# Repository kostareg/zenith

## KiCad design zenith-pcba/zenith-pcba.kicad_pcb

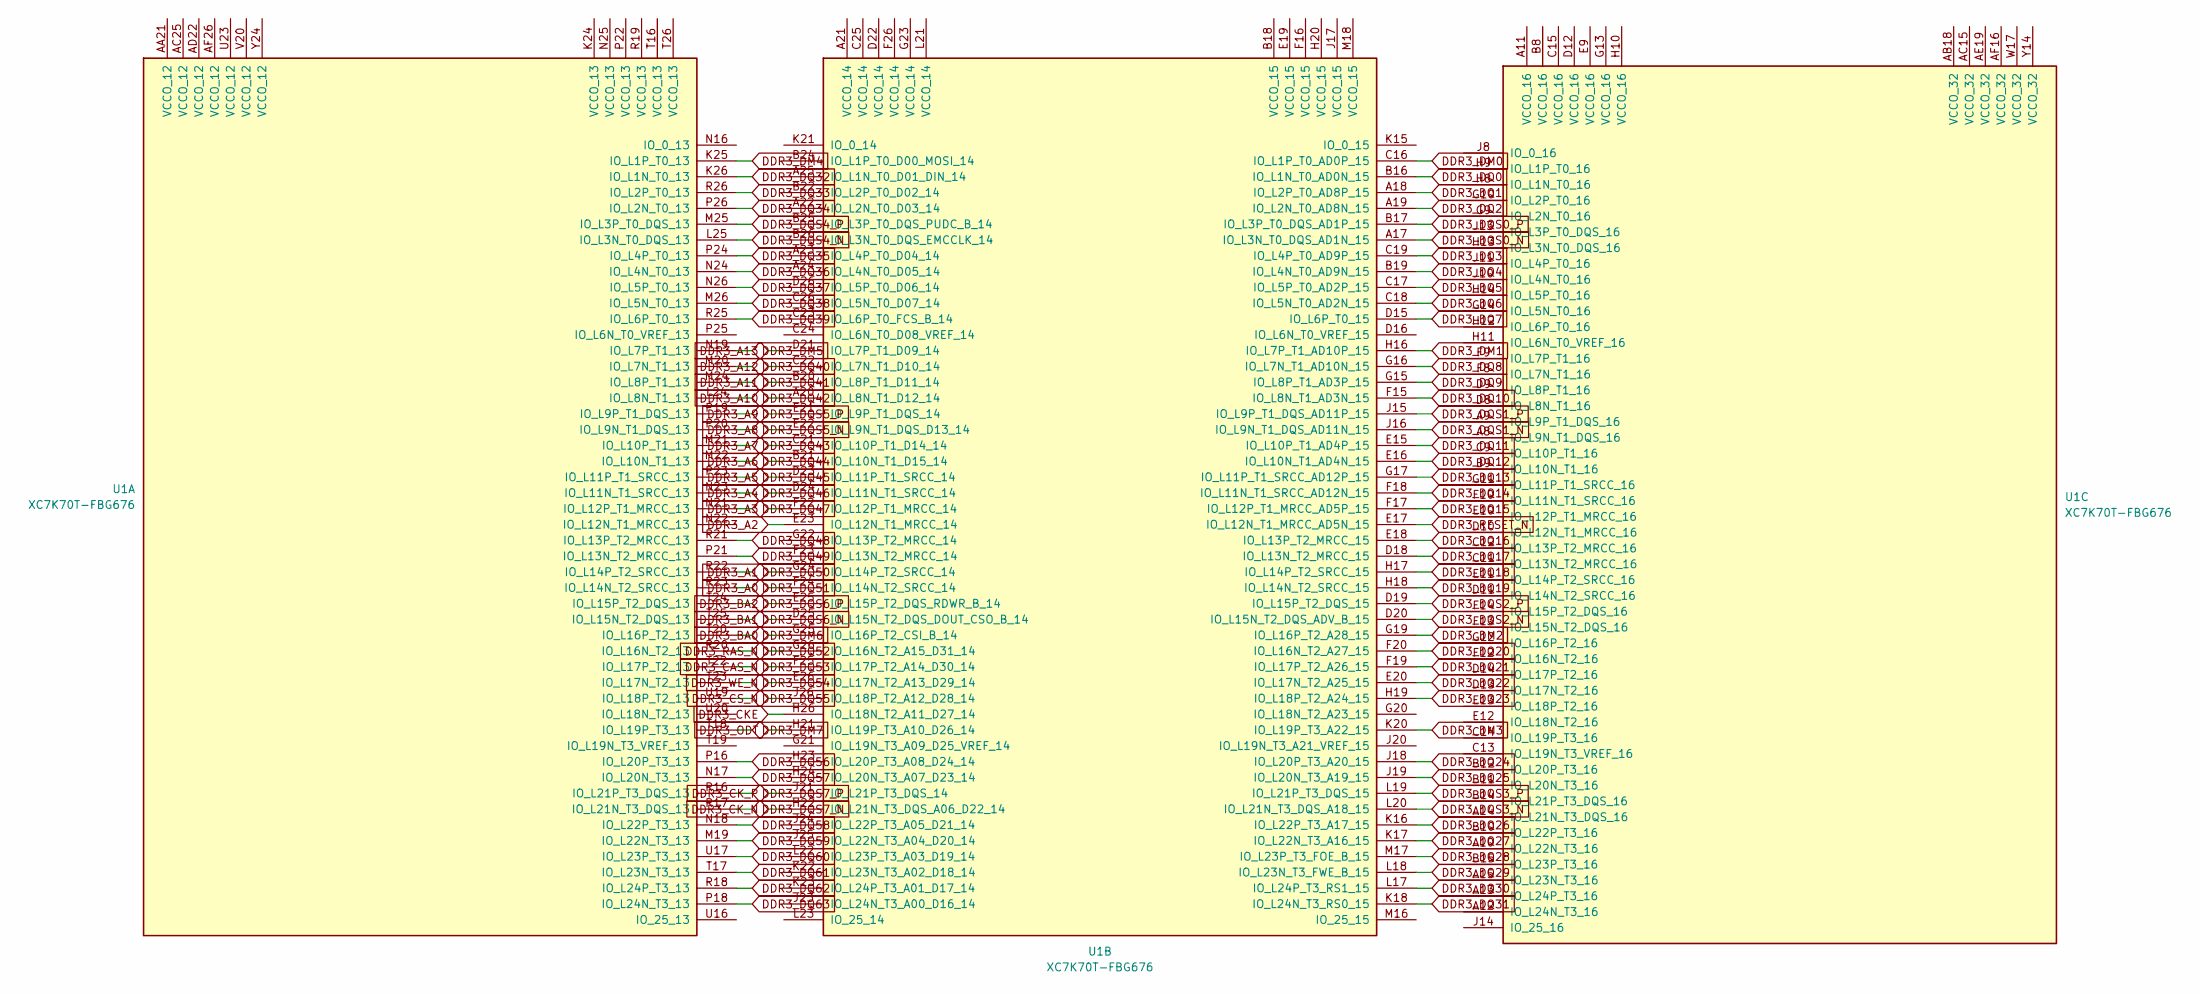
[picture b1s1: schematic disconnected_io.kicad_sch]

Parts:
U1: XC7K70T-FBG676; FBGA-676_L27.0-W27.0-R26-C26-P1.00-BL

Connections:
DDR3_A0: U1.F24 (IO_L14N_T2_SRCC_14); also elsewhere on the board
DDR3_A1: U1.G24 (IO_L14P_T2_SRCC_14); also elsewhere on the board
DDR3_A2: U1.E23 (IO_L12N_T1_MRCC_14); also elsewhere on the board
DDR3_A3: U1.F22 (IO_L12P_T1_MRCC_14); also elsewhere on the board
DDR3_A4: U1.D24 (IO_L11N_T1_SRCC_14); also elsewhere on the board
DDR3_A5: U1.D23 (IO_L11P_T1_SRCC_14); also elsewhere on the board
DDR3_A6: U1.B21 (IO_L10N_T1_D15_14); also elsewhere on the board
DDR3_A7: U1.C21 (IO_L10P_T1_D14_14); also elsewhere on the board
DDR3_A8: U1.E22 (IO_L9N_T1_DQS_D13_14); also elsewhere on the board
DDR3_A9: U1.E21 (IO_L9P_T1_DQS_14); also elsewhere on the board
DDR3_A10: U1.A20 (IO_L8N_T1_D12_14); also elsewhere on the board
DDR3_A11: U1.B20 (IO_L8P_T1_D11_14); also elsewhere on the board
DDR3_A12: U1.C22 (IO_L7N_T1_D10_14); also elsewhere on the board
DDR3_A13: U1.D21 (IO_L7P_T1_D09_14); also elsewhere on the board
DDR3_BA0: U1.G25 (IO_L16P_T2_CSI_B_14); also elsewhere on the board
DDR3_BA1: U1.D25 (IO_L15N_T2_DQS_DOUT_CSO_B_14); also elsewhere on the board
DDR3_BA2: U1.E25 (IO_L15P_T2_DQS_RDWR_B_14); also elsewhere on the board
DDR3_CAS_N: U1.F25 (IO_L17P_T2_A14_D30_14); also elsewhere on the board
DDR3_CKE: U1.H26 (IO_L18N_T2_A11_D27_14); also elsewhere on the board
DDR3_CK_N: U1.H22 (IO_L21N_T3_DQS_A06_D22_14); also elsewhere on the board
DDR3_CK_P: U1.J21 (IO_L21P_T3_DQS_14); also elsewhere on the board
DDR3_CS_N: U1.J26 (IO_L18P_T2_A12_D28_14); also elsewhere on the board
DDR3_DM0: U1.C16 (IO_L1P_T0_AD0P_15); also elsewhere on the board
DDR3_DM1: U1.H16 (IO_L7P_T1_AD10P_15); also elsewhere on the board
DDR3_DM2: U1.G19 (IO_L16P_T2_A28_15); also elsewhere on the board
DDR3_DM3: U1.K20 (IO_L19P_T3_A22_15); also elsewhere on the board
DDR3_DM4: U1.K25 (IO_L1P_T0_13); also elsewhere on the board
DDR3_DM5: U1.N19 (IO_L7P_T1_13); also elsewhere on the board
DDR3_DM6: U1.T20 (IO_L16P_T2_13); also elsewhere on the board
DDR3_DM7: U1.T18 (IO_L19P_T3_13); also elsewhere on the board
DDR3_DQ0: U1.B16 (IO_L1N_T0_AD0N_15); also elsewhere on the board
DDR3_DQ1: U1.A18 (IO_L2P_T0_AD8P_15); also elsewhere on the board
DDR3_DQ2: U1.A19 (IO_L2N_T0_AD8N_15); also elsewhere on the board
DDR3_DQ3: U1.C19 (IO_L4P_T0_AD9P_15); also elsewhere on the board
DDR3_DQ4: U1.B19 (IO_L4N_T0_AD9N_15); also elsewhere on the board
DDR3_DQ5: U1.C17 (IO_L5P_T0_AD2P_15); also elsewhere on the board
DDR3_DQ6: U1.C18 (IO_L5N_T0_AD2N_15); also elsewhere on the board
DDR3_DQ7: U1.D15 (IO_L6P_T0_15); also elsewhere on the board
DDR3_DQ8: U1.G16 (IO_L7N_T1_AD10N_15); also elsewhere on the board
DDR3_DQ9: U1.G15 (IO_L8P_T1_AD3P_15); also elsewhere on the board
DDR3_DQ10: U1.F15 (IO_L8N_T1_AD3N_15); also elsewhere on the board
DDR3_DQ11: U1.E15 (IO_L10P_T1_AD4P_15); also elsewhere on the board
DDR3_DQ12: U1.E16 (IO_L10N_T1_AD4N_15); also elsewhere on the board
DDR3_DQ13: U1.G17 (IO_L11P_T1_SRCC_AD12P_15); also elsewhere on the board
DDR3_DQ14: U1.F18 (IO_L11N_T1_SRCC_AD12N_15); also elsewhere on the board
DDR3_DQ15: U1.F17 (IO_L12P_T1_MRCC_AD5P_15); also elsewhere on the board
DDR3_DQ16: U1.E18 (IO_L13P_T2_MRCC_15); also elsewhere on the board
DDR3_DQ17: U1.D18 (IO_L13N_T2_MRCC_15); also elsewhere on the board
DDR3_DQ18: U1.H17 (IO_L14P_T2_SRCC_15); also elsewhere on the board
DDR3_DQ19: U1.H18 (IO_L14N_T2_SRCC_15); also elsewhere on the board
DDR3_DQ20: U1.F20 (IO_L16N_T2_A27_15); also elsewhere on the board
DDR3_DQ21: U1.F19 (IO_L17P_T2_A26_15); also elsewhere on the board
DDR3_DQ22: U1.E20 (IO_L17N_T2_A25_15); also elsewhere on the board
DDR3_DQ23: U1.H19 (IO_L18P_T2_A24_15); also elsewhere on the board
DDR3_DQ24: U1.J18 (IO_L20P_T3_A20_15); also elsewhere on the board
DDR3_DQ25: U1.J19 (IO_L20N_T3_A19_15); also elsewhere on the board
DDR3_DQ26: U1.K16 (IO_L22P_T3_A17_15); also elsewhere on the board
DDR3_DQ27: U1.K17 (IO_L22N_T3_A16_15); also elsewhere on the board
DDR3_DQ28: U1.M17 (IO_L23P_T3_FOE_B_15); also elsewhere on the board
DDR3_DQ29: U1.L18 (IO_L23N_T3_FWE_B_15); also elsewhere on the board
DDR3_DQ30: U1.L17 (IO_L24P_T3_RS1_15); also elsewhere on the board
DDR3_DQ31: U1.K18 (IO_L24N_T3_RS0_15); also elsewhere on the board
DDR3_DQ32: U1.K26 (IO_L1N_T0_13); also elsewhere on the board
DDR3_DQ33: U1.R26 (IO_L2P_T0_13); also elsewhere on the board
DDR3_DQ34: U1.P26 (IO_L2N_T0_13); also elsewhere on the board
DDR3_DQ35: U1.P24 (IO_L4P_T0_13); also elsewhere on the board
DDR3_DQ36: U1.N24 (IO_L4N_T0_13); also elsewhere on the board
DDR3_DQ37: U1.N26 (IO_L5P_T0_13); also elsewhere on the board
DDR3_DQ38: U1.M26 (IO_L5N_T0_13); also elsewhere on the board
DDR3_DQ39: U1.R25 (IO_L6P_T0_13); also elsewhere on the board
DDR3_DQ40: U1.M20 (IO_L7N_T1_13); also elsewhere on the board
DDR3_DQ41: U1.M24 (IO_L8P_T1_13); also elsewhere on the board
DDR3_DQ42: U1.L24 (IO_L8N_T1_13); also elsewhere on the board
DDR3_DQ43: U1.M21 (IO_L10P_T1_13); also elsewhere on the board
DDR3_DQ44: U1.M22 (IO_L10N_T1_13); also elsewhere on the board
DDR3_DQ45: U1.P23 (IO_L11P_T1_SRCC_13); also elsewhere on the board
DDR3_DQ46: U1.N23 (IO_L11N_T1_SRCC_13); also elsewhere on the board
DDR3_DQ47: U1.N21 (IO_L12P_T1_MRCC_13); also elsewhere on the board
DDR3_DQ48: U1.R21 (IO_L13P_T2_MRCC_13); also elsewhere on the board
DDR3_DQ49: U1.P21 (IO_L13N_T2_MRCC_13); also elsewhere on the board
DDR3_DQ50: U1.R22 (IO_L14P_T2_SRCC_13); also elsewhere on the board
DDR3_DQ51: U1.R23 (IO_L14N_T2_SRCC_13); also elsewhere on the board
DDR3_DQ52: U1.R20 (IO_L16N_T2_13); also elsewhere on the board
DDR3_DQ53: U1.T22 (IO_L17P_T2_13); also elsewhere on the board
DDR3_DQ54: U1.T23 (IO_L17N_T2_13); also elsewhere on the board
DDR3_DQ55: U1.U19 (IO_L18P_T2_13); also elsewhere on the board
DDR3_DQ56: U1.P16 (IO_L20P_T3_13); also elsewhere on the board
DDR3_DQ57: U1.N17 (IO_L20N_T3_13); also elsewhere on the board
DDR3_DQ58: U1.N18 (IO_L22P_T3_13); also elsewhere on the board
DDR3_DQ59: U1.M19 (IO_L22N_T3_13); also elsewhere on the board
DDR3_DQ60: U1.U17 (IO_L23P_T3_13); also elsewhere on the board
DDR3_DQ61: U1.T17 (IO_L23N_T3_13); also elsewhere on the board
DDR3_DQ62: U1.R18 (IO_L24P_T3_13); also elsewhere on the board
DDR3_DQ63: U1.P18 (IO_L24N_T3_13); also elsewhere on the board
DDR3_DQS0_N: U1.A17 (IO_L3N_T0_DQS_AD1N_15); also elsewhere on the board
DDR3_DQS0_P: U1.B17 (IO_L3P_T0_DQS_AD1P_15); also elsewhere on the board
DDR3_DQS1_N: U1.J16 (IO_L9N_T1_DQS_AD11N_15); also elsewhere on the board
DDR3_DQS1_P: U1.J15 (IO_L9P_T1_DQS_AD11P_15); also elsewhere on the board
DDR3_DQS2_N: U1.D20 (IO_L15N_T2_DQS_ADV_B_15); also elsewhere on the board
DDR3_DQS2_P: U1.D19 (IO_L15P_T2_DQS_15); also elsewhere on the board
DDR3_DQS3_N: U1.L20 (IO_L21N_T3_DQS_A18_15); also elsewhere on the board
DDR3_DQS3_P: U1.L19 (IO_L21P_T3_DQS_15); also elsewhere on the board
DDR3_DQS4_N: U1.L25 (IO_L3N_T0_DQS_13); also elsewhere on the board
DDR3_DQS4_P: U1.M25 (IO_L3P_T0_DQS_13); also elsewhere on the board
DDR3_DQS5_N: U1.P20 (IO_L9N_T1_DQS_13); also elsewhere on the board
DDR3_DQS5_P: U1.P19 (IO_L9P_T1_DQS_13); also elsewhere on the board
DDR3_DQS6_N: U1.T25 (IO_L15N_T2_DQS_13); also elsewhere on the board
DDR3_DQS6_P: U1.T24 (IO_L15P_T2_DQS_13); also elsewhere on the board
DDR3_DQS7_N: U1.R17 (IO_L21N_T3_DQS_13); also elsewhere on the board
DDR3_DQS7_P: U1.R16 (IO_L21P_T3_DQS_13); also elsewhere on the board
DDR3_ODT: U1.H21 (IO_L19P_T3_A10_D26_14); also elsewhere on the board
DDR3_RAS_N: U1.G26 (IO_L16N_T2_A15_D31_14); also elsewhere on the board
DDR3_RESET_N: U1.E17 (IO_L12N_T1_MRCC_AD5N_15); also elsewhere on the board
DDR3_WE_N: U1.E26 (IO_L17N_T2_A13_D29_14); also elsewhere on the board

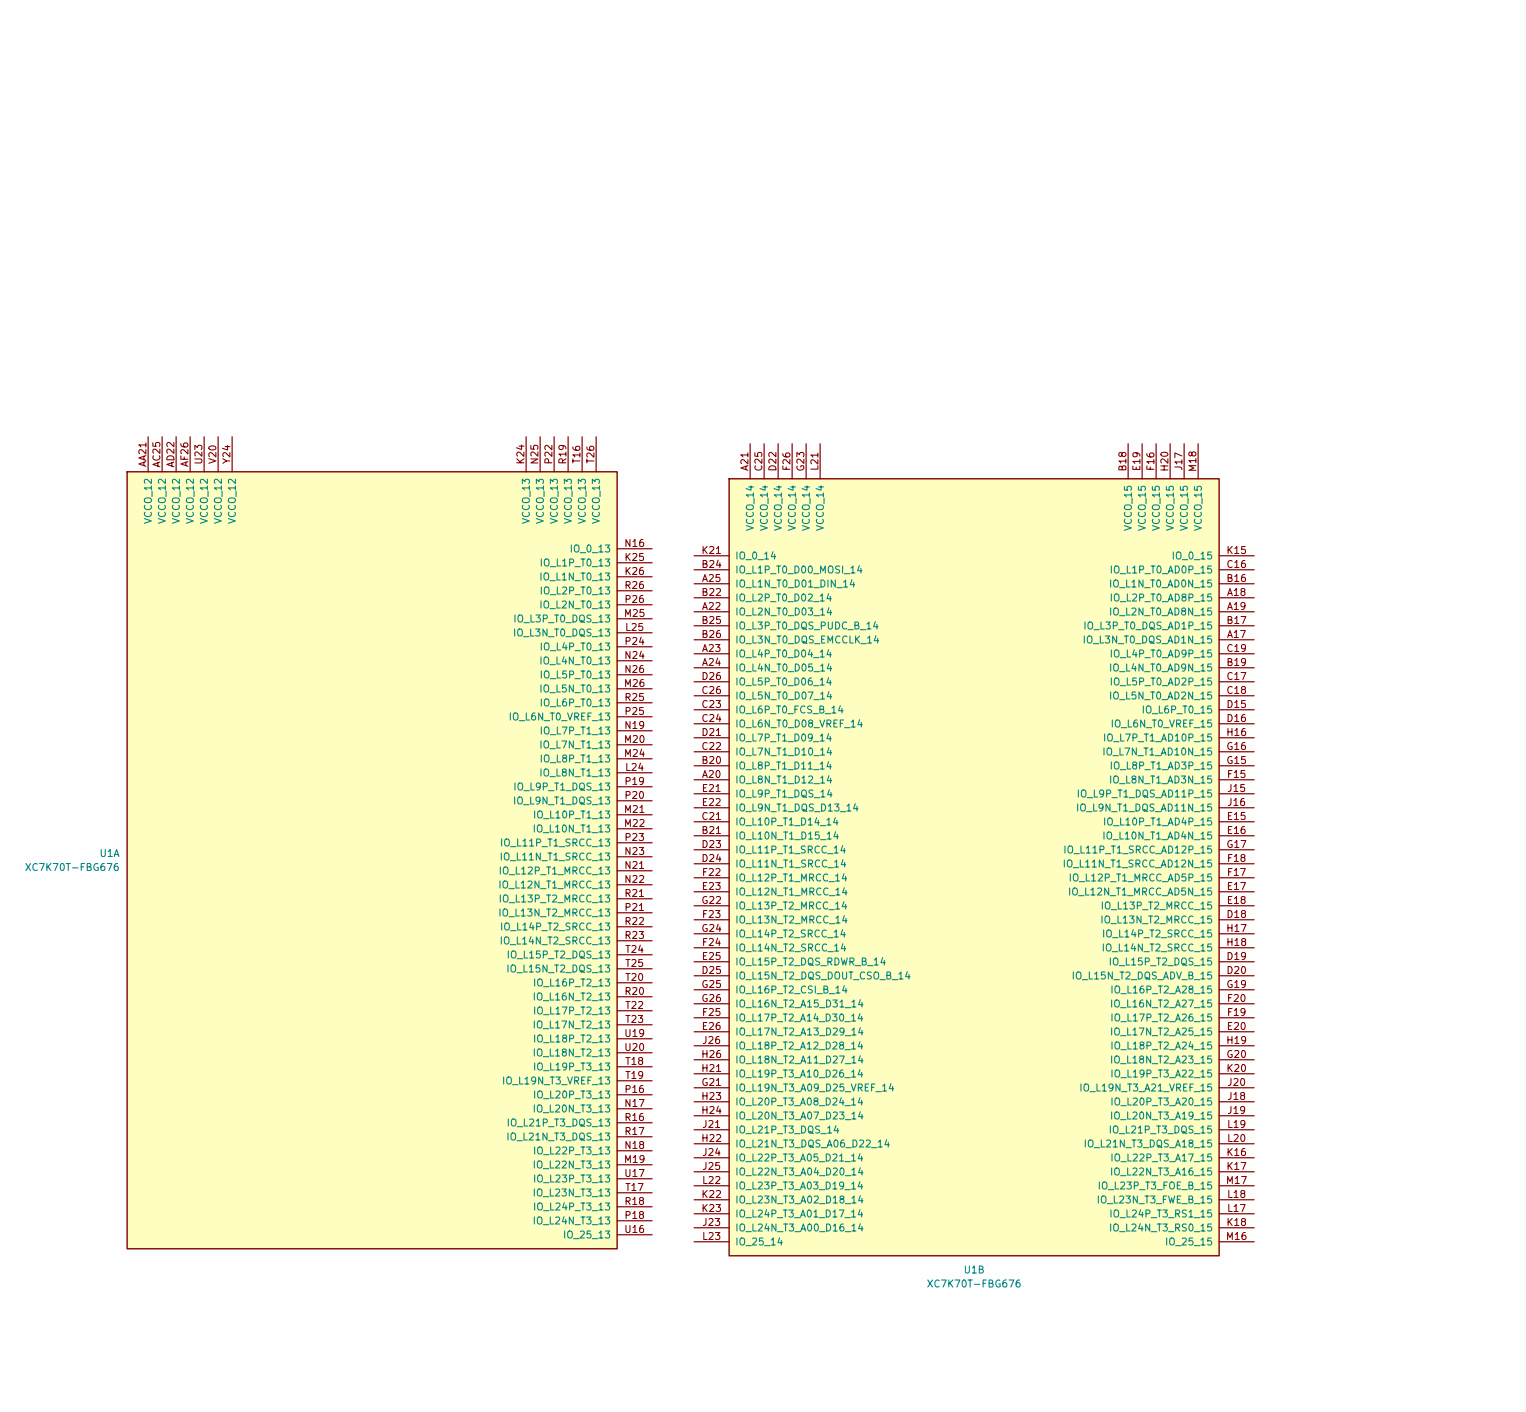
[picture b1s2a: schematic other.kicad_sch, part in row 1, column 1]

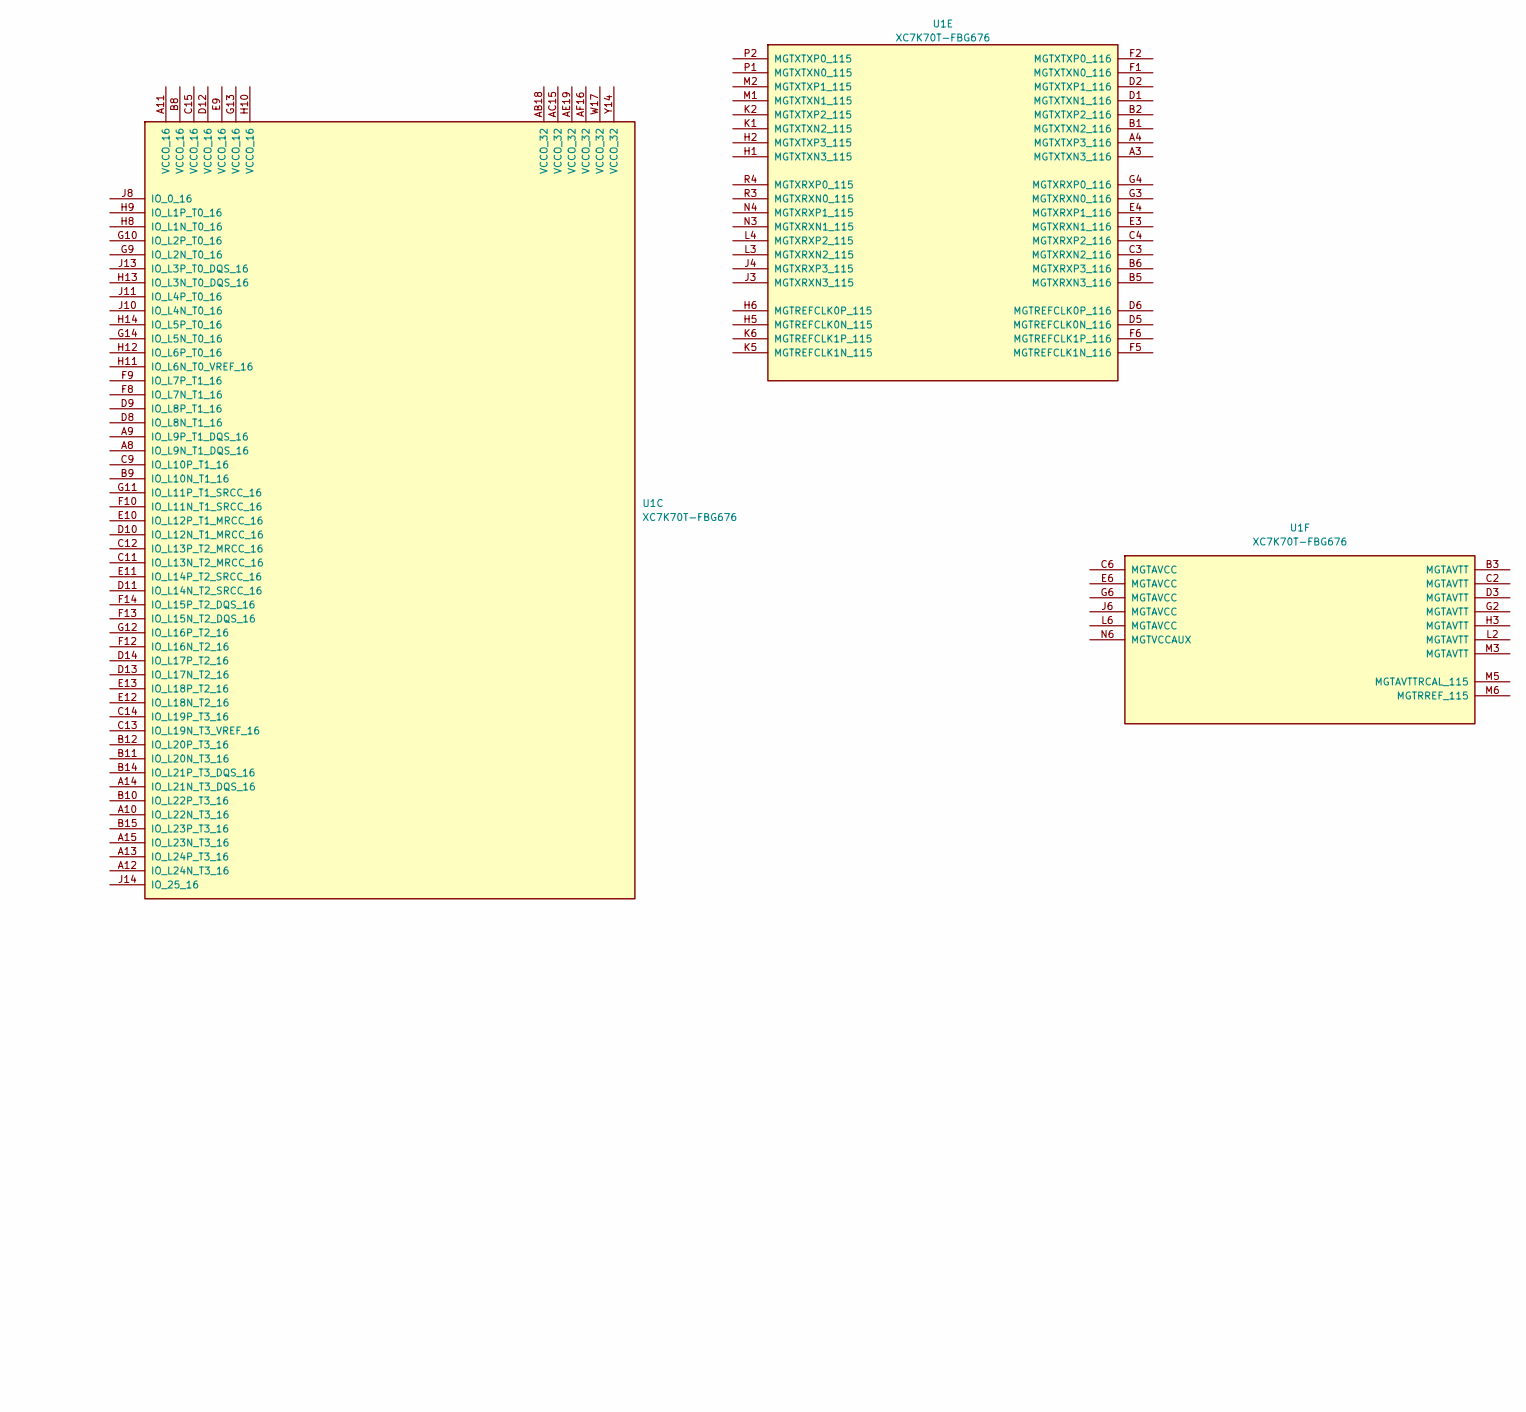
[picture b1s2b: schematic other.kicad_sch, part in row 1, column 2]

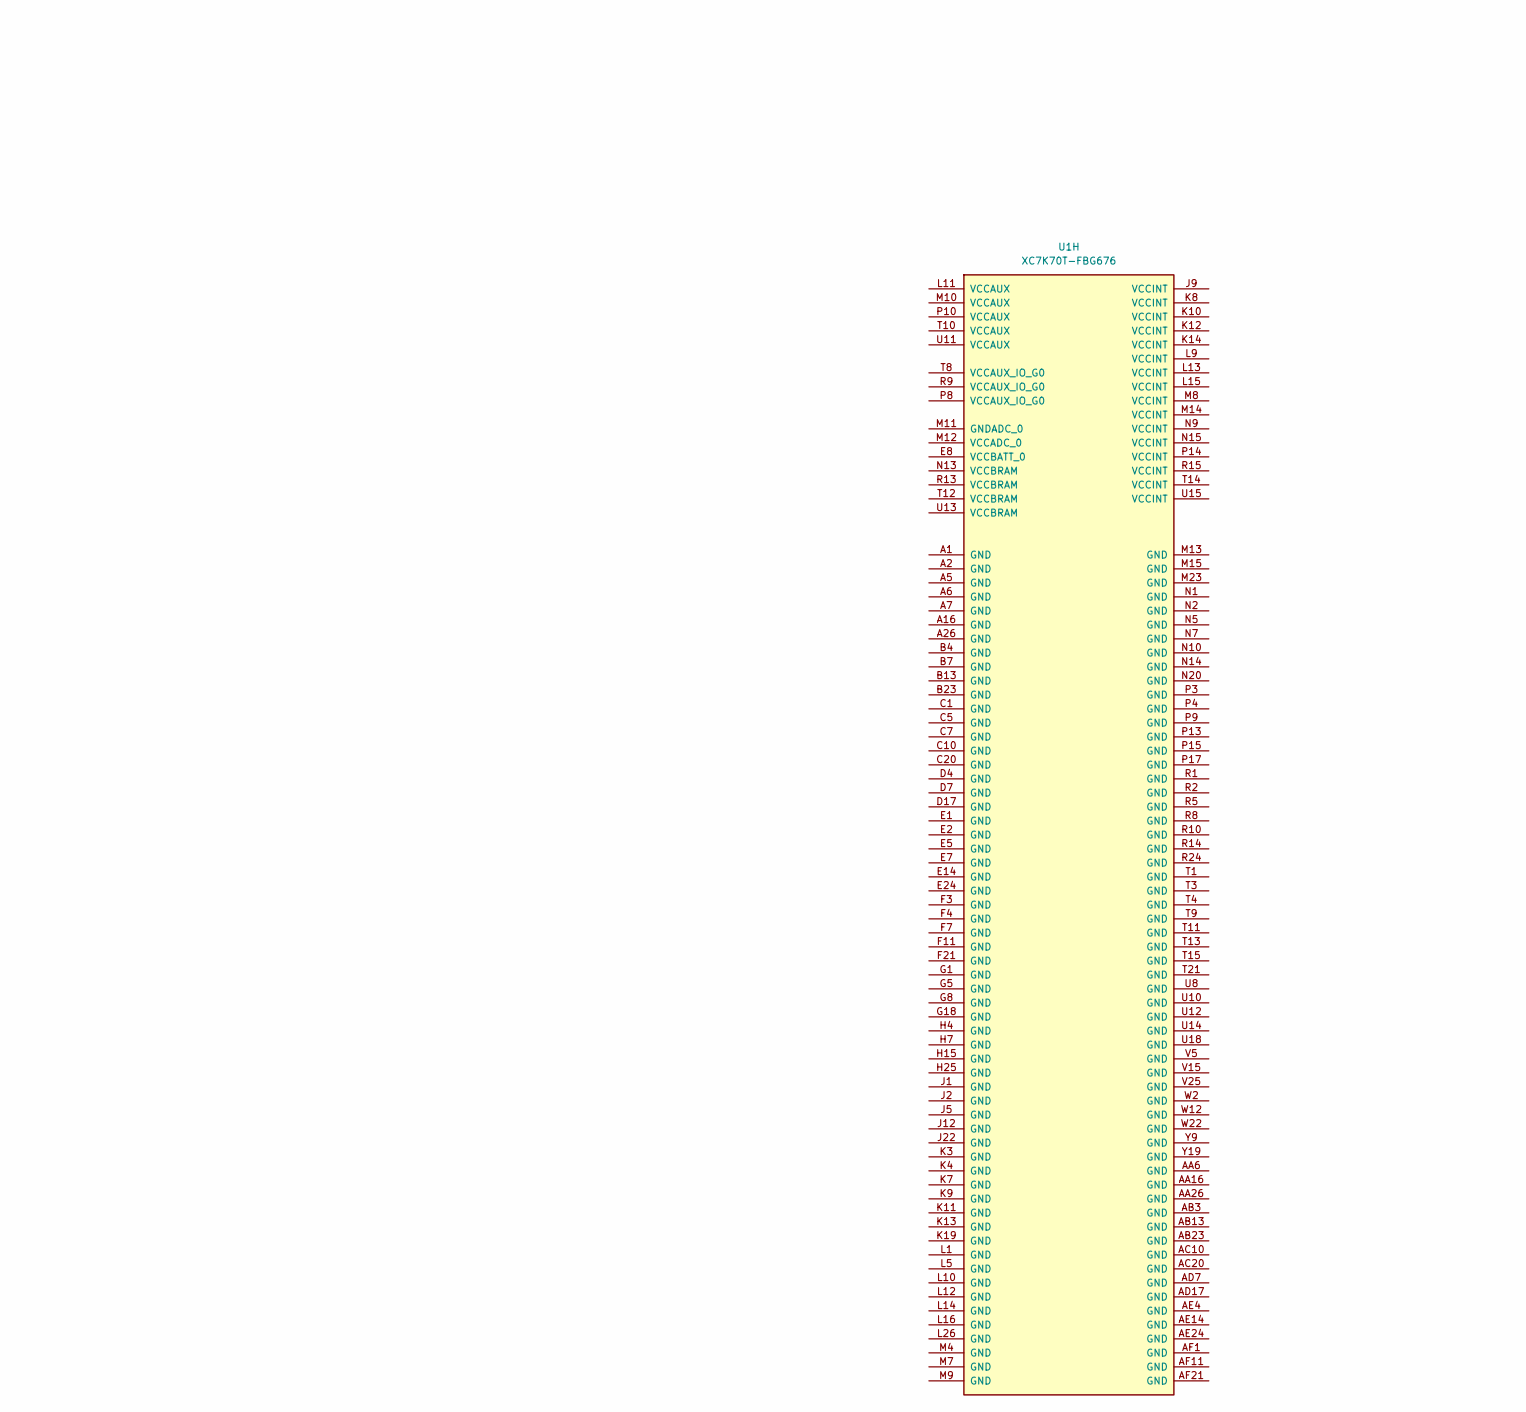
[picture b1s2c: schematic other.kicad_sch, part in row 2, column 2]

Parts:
U1: XC7K70T-FBG676; FBGA-676_L27.0-W27.0-R26-C26-P1.00-BL

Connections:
DDR3_A0: U1.F24 (IO_L14N_T2_SRCC_14); also elsewhere on the board
DDR3_A1: U1.G24 (IO_L14P_T2_SRCC_14); also elsewhere on the board
DDR3_A2: U1.E23 (IO_L12N_T1_MRCC_14); also elsewhere on the board
DDR3_A3: U1.F22 (IO_L12P_T1_MRCC_14); also elsewhere on the board
DDR3_A4: U1.D24 (IO_L11N_T1_SRCC_14); also elsewhere on the board
DDR3_A5: U1.D23 (IO_L11P_T1_SRCC_14); also elsewhere on the board
DDR3_A6: U1.B21 (IO_L10N_T1_D15_14); also elsewhere on the board
DDR3_A7: U1.C21 (IO_L10P_T1_D14_14); also elsewhere on the board
DDR3_A8: U1.E22 (IO_L9N_T1_DQS_D13_14); also elsewhere on the board
DDR3_A9: U1.E21 (IO_L9P_T1_DQS_14); also elsewhere on the board
DDR3_A10: U1.A20 (IO_L8N_T1_D12_14); also elsewhere on the board
DDR3_A11: U1.B20 (IO_L8P_T1_D11_14); also elsewhere on the board
DDR3_A12: U1.C22 (IO_L7N_T1_D10_14); also elsewhere on the board
DDR3_A13: U1.D21 (IO_L7P_T1_D09_14); also elsewhere on the board
DDR3_BA0: U1.G25 (IO_L16P_T2_CSI_B_14); also elsewhere on the board
DDR3_BA1: U1.D25 (IO_L15N_T2_DQS_DOUT_CSO_B_14); also elsewhere on the board
DDR3_BA2: U1.E25 (IO_L15P_T2_DQS_RDWR_B_14); also elsewhere on the board
DDR3_CAS_N: U1.F25 (IO_L17P_T2_A14_D30_14); also elsewhere on the board
DDR3_CKE: U1.H26 (IO_L18N_T2_A11_D27_14); also elsewhere on the board
DDR3_CK_N: U1.H22 (IO_L21N_T3_DQS_A06_D22_14); also elsewhere on the board
DDR3_CK_P: U1.J21 (IO_L21P_T3_DQS_14); also elsewhere on the board
DDR3_CS_N: U1.J26 (IO_L18P_T2_A12_D28_14); also elsewhere on the board
DDR3_DM0: U1.C16 (IO_L1P_T0_AD0P_15); also elsewhere on the board
DDR3_DM1: U1.H16 (IO_L7P_T1_AD10P_15); also elsewhere on the board
DDR3_DM2: U1.G19 (IO_L16P_T2_A28_15); also elsewhere on the board
DDR3_DM3: U1.K20 (IO_L19P_T3_A22_15); also elsewhere on the board
DDR3_DM4: U1.K25 (IO_L1P_T0_13); also elsewhere on the board
DDR3_DM5: U1.N19 (IO_L7P_T1_13); also elsewhere on the board
DDR3_DM6: U1.T20 (IO_L16P_T2_13); also elsewhere on the board
DDR3_DM7: U1.T18 (IO_L19P_T3_13); also elsewhere on the board
DDR3_DQ0: U1.B16 (IO_L1N_T0_AD0N_15); also elsewhere on the board
DDR3_DQ1: U1.A18 (IO_L2P_T0_AD8P_15); also elsewhere on the board
DDR3_DQ2: U1.A19 (IO_L2N_T0_AD8N_15); also elsewhere on the board
DDR3_DQ3: U1.C19 (IO_L4P_T0_AD9P_15); also elsewhere on the board
DDR3_DQ4: U1.B19 (IO_L4N_T0_AD9N_15); also elsewhere on the board
DDR3_DQ5: U1.C17 (IO_L5P_T0_AD2P_15); also elsewhere on the board
DDR3_DQ6: U1.C18 (IO_L5N_T0_AD2N_15); also elsewhere on the board
DDR3_DQ7: U1.D15 (IO_L6P_T0_15); also elsewhere on the board
DDR3_DQ8: U1.G16 (IO_L7N_T1_AD10N_15); also elsewhere on the board
DDR3_DQ9: U1.G15 (IO_L8P_T1_AD3P_15); also elsewhere on the board
DDR3_DQ10: U1.F15 (IO_L8N_T1_AD3N_15); also elsewhere on the board
DDR3_DQ11: U1.E15 (IO_L10P_T1_AD4P_15); also elsewhere on the board
DDR3_DQ12: U1.E16 (IO_L10N_T1_AD4N_15); also elsewhere on the board
DDR3_DQ13: U1.G17 (IO_L11P_T1_SRCC_AD12P_15); also elsewhere on the board
DDR3_DQ14: U1.F18 (IO_L11N_T1_SRCC_AD12N_15); also elsewhere on the board
DDR3_DQ15: U1.F17 (IO_L12P_T1_MRCC_AD5P_15); also elsewhere on the board
DDR3_DQ16: U1.E18 (IO_L13P_T2_MRCC_15); also elsewhere on the board
DDR3_DQ17: U1.D18 (IO_L13N_T2_MRCC_15); also elsewhere on the board
DDR3_DQ18: U1.H17 (IO_L14P_T2_SRCC_15); also elsewhere on the board
DDR3_DQ19: U1.H18 (IO_L14N_T2_SRCC_15); also elsewhere on the board
DDR3_DQ20: U1.F20 (IO_L16N_T2_A27_15); also elsewhere on the board
DDR3_DQ21: U1.F19 (IO_L17P_T2_A26_15); also elsewhere on the board
DDR3_DQ22: U1.E20 (IO_L17N_T2_A25_15); also elsewhere on the board
DDR3_DQ23: U1.H19 (IO_L18P_T2_A24_15); also elsewhere on the board
DDR3_DQ24: U1.J18 (IO_L20P_T3_A20_15); also elsewhere on the board
DDR3_DQ25: U1.J19 (IO_L20N_T3_A19_15); also elsewhere on the board
DDR3_DQ26: U1.K16 (IO_L22P_T3_A17_15); also elsewhere on the board
DDR3_DQ27: U1.K17 (IO_L22N_T3_A16_15); also elsewhere on the board
DDR3_DQ28: U1.M17 (IO_L23P_T3_FOE_B_15); also elsewhere on the board
DDR3_DQ29: U1.L18 (IO_L23N_T3_FWE_B_15); also elsewhere on the board
DDR3_DQ30: U1.L17 (IO_L24P_T3_RS1_15); also elsewhere on the board
DDR3_DQ31: U1.K18 (IO_L24N_T3_RS0_15); also elsewhere on the board
DDR3_DQ32: U1.K26 (IO_L1N_T0_13); also elsewhere on the board
DDR3_DQ33: U1.R26 (IO_L2P_T0_13); also elsewhere on the board
DDR3_DQ34: U1.P26 (IO_L2N_T0_13); also elsewhere on the board
DDR3_DQ35: U1.P24 (IO_L4P_T0_13); also elsewhere on the board
DDR3_DQ36: U1.N24 (IO_L4N_T0_13); also elsewhere on the board
DDR3_DQ37: U1.N26 (IO_L5P_T0_13); also elsewhere on the board
DDR3_DQ38: U1.M26 (IO_L5N_T0_13); also elsewhere on the board
DDR3_DQ39: U1.R25 (IO_L6P_T0_13); also elsewhere on the board
DDR3_DQ40: U1.M20 (IO_L7N_T1_13); also elsewhere on the board
DDR3_DQ41: U1.M24 (IO_L8P_T1_13); also elsewhere on the board
DDR3_DQ42: U1.L24 (IO_L8N_T1_13); also elsewhere on the board
DDR3_DQ43: U1.M21 (IO_L10P_T1_13); also elsewhere on the board
DDR3_DQ44: U1.M22 (IO_L10N_T1_13); also elsewhere on the board
DDR3_DQ45: U1.P23 (IO_L11P_T1_SRCC_13); also elsewhere on the board
DDR3_DQ46: U1.N23 (IO_L11N_T1_SRCC_13); also elsewhere on the board
DDR3_DQ47: U1.N21 (IO_L12P_T1_MRCC_13); also elsewhere on the board
DDR3_DQ48: U1.R21 (IO_L13P_T2_MRCC_13); also elsewhere on the board
DDR3_DQ49: U1.P21 (IO_L13N_T2_MRCC_13); also elsewhere on the board
DDR3_DQ50: U1.R22 (IO_L14P_T2_SRCC_13); also elsewhere on the board
DDR3_DQ51: U1.R23 (IO_L14N_T2_SRCC_13); also elsewhere on the board
DDR3_DQ52: U1.R20 (IO_L16N_T2_13); also elsewhere on the board
DDR3_DQ53: U1.T22 (IO_L17P_T2_13); also elsewhere on the board
DDR3_DQ54: U1.T23 (IO_L17N_T2_13); also elsewhere on the board
DDR3_DQ55: U1.U19 (IO_L18P_T2_13); also elsewhere on the board
DDR3_DQ56: U1.P16 (IO_L20P_T3_13); also elsewhere on the board
DDR3_DQ57: U1.N17 (IO_L20N_T3_13); also elsewhere on the board
DDR3_DQ58: U1.N18 (IO_L22P_T3_13); also elsewhere on the board
DDR3_DQ59: U1.M19 (IO_L22N_T3_13); also elsewhere on the board
DDR3_DQ60: U1.U17 (IO_L23P_T3_13); also elsewhere on the board
DDR3_DQ61: U1.T17 (IO_L23N_T3_13); also elsewhere on the board
DDR3_DQ62: U1.R18 (IO_L24P_T3_13); also elsewhere on the board
DDR3_DQ63: U1.P18 (IO_L24N_T3_13); also elsewhere on the board
DDR3_DQS0_N: U1.A17 (IO_L3N_T0_DQS_AD1N_15); also elsewhere on the board
DDR3_DQS0_P: U1.B17 (IO_L3P_T0_DQS_AD1P_15); also elsewhere on the board
DDR3_DQS1_N: U1.J16 (IO_L9N_T1_DQS_AD11N_15); also elsewhere on the board
DDR3_DQS1_P: U1.J15 (IO_L9P_T1_DQS_AD11P_15); also elsewhere on the board
DDR3_DQS2_N: U1.D20 (IO_L15N_T2_DQS_ADV_B_15); also elsewhere on the board
DDR3_DQS2_P: U1.D19 (IO_L15P_T2_DQS_15); also elsewhere on the board
DDR3_DQS3_N: U1.L20 (IO_L21N_T3_DQS_A18_15); also elsewhere on the board
DDR3_DQS3_P: U1.L19 (IO_L21P_T3_DQS_15); also elsewhere on the board
DDR3_DQS4_N: U1.L25 (IO_L3N_T0_DQS_13); also elsewhere on the board
DDR3_DQS4_P: U1.M25 (IO_L3P_T0_DQS_13); also elsewhere on the board
DDR3_DQS5_N: U1.P20 (IO_L9N_T1_DQS_13); also elsewhere on the board
DDR3_DQS5_P: U1.P19 (IO_L9P_T1_DQS_13); also elsewhere on the board
DDR3_DQS6_N: U1.T25 (IO_L15N_T2_DQS_13); also elsewhere on the board
DDR3_DQS6_P: U1.T24 (IO_L15P_T2_DQS_13); also elsewhere on the board
DDR3_DQS7_N: U1.R17 (IO_L21N_T3_DQS_13); also elsewhere on the board
DDR3_DQS7_P: U1.R16 (IO_L21P_T3_DQS_13); also elsewhere on the board
DDR3_ODT: U1.H21 (IO_L19P_T3_A10_D26_14); also elsewhere on the board
DDR3_RAS_N: U1.G26 (IO_L16N_T2_A15_D31_14); also elsewhere on the board
DDR3_RESET_N: U1.E17 (IO_L12N_T1_MRCC_AD5N_15); also elsewhere on the board
DDR3_WE_N: U1.E26 (IO_L17N_T2_A13_D29_14); also elsewhere on the board
GND: U1.A1 (GND), U1.A2 (GND), U1.A5 (GND), U1.A6 (GND), U1.A7 (GND), U1.A16 (GND), U1.A26 (GND), U1.AA6 (GND), U1.AA16 (GND), U1.AA26 (GND), U1.AB3 (GND), U1.AB13 (GND), U1.AB23 (GND), U1.AC10 (GND), U1.AC20 (GND), U1.AD7 (GND), U1.AD17 (GND), U1.AE4 (GND), U1.AE14 (GND), U1.AE24 (GND), U1.AF1 (GND), U1.AF11 (GND), U1.AF21 (GND), U1.B4 (GND), U1.B7 (GND), U1.B13 (GND), U1.B23 (GND), U1.C1 (GND), U1.C5 (GND), U1.C7 (GND), U1.C10 (GND), U1.C20 (GND), U1.D4 (GND), U1.D7 (GND), U1.D17 (GND), U1.E1 (GND), U1.E2 (GND), U1.E5 (GND), U1.E7 (GND), U1.E14 (GND), U1.E24 (GND), U1.F3 (GND), U1.F4 (GND), U1.F7 (GND), U1.F11 (GND), U1.F21 (GND), U1.G1 (GND), U1.G5 (GND), U1.G8 (GND), U1.G18 (GND), U1.H4 (GND), U1.H7 (GND), U1.H15 (GND), U1.H25 (GND), U1.J1 (GND), U1.J2 (GND), U1.J5 (GND), U1.J12 (GND), U1.J22 (GND), U1.K3 (GND), U1.K4 (GND), U1.K7 (GND), U1.K9 (GND), U1.K11 (GND), U1.K13 (GND), U1.K19 (GND), U1.L1 (GND), U1.L5 (GND), U1.L10 (GND), U1.L12 (GND), U1.L14 (GND), U1.L16 (GND), U1.L26 (GND), U1.M4 (GND), U1.M7 (GND), U1.M9 (GND), U1.M11 (GNDADC_0), U1.M13 (GND), U1.M15 (GND), U1.M23 (GND), U1.N1 (GND), U1.N2 (GND), U1.N5 (GND), U1.N7 (GND), U1.N10 (GND), U1.N14 (GND), U1.N20 (GND), U1.P3 (GND), U1.P4 (GND), U1.P9 (GND), U1.P13 (GND), U1.P15 (GND), U1.P17 (GND), U1.R1 (GND), U1.R2 (GND), U1.R5 (GND), U1.R8 (GND), U1.R10 (GND), U1.R14 (GND), U1.R24 (GND), U1.T1 (GND), U1.T3 (GND), U1.T4 (GND), U1.T9 (GND), U1.T11 (GND), U1.T13 (GND), U1.T15 (GND), U1.T21 (GND), U1.U8 (GND), U1.U10 (GND), U1.U12 (GND), U1.U14 (GND), U1.U18 (GND), U1.V5 (GND), U1.V15 (GND), U1.V25 (GND), U1.W2 (GND), U1.W12 (GND), U1.W22 (GND), U1.Y9 (GND), U1.Y19 (GND); also elsewhere on the board
VCC1.0: U1.J9 (VCCINT), U1.K8 (VCCINT), U1.K10 (VCCINT), U1.K12 (VCCINT), U1.K14 (VCCINT), U1.L9 (VCCINT), U1.L13 (VCCINT), U1.L15 (VCCINT), U1.M8 (VCCINT), U1.M14 (VCCINT), U1.N9 (VCCINT), U1.N13 (VCCBRAM), U1.N15 (VCCINT), U1.P14 (VCCINT), U1.R13 (VCCBRAM), U1.R15 (VCCINT), U1.T12 (VCCBRAM), U1.T14 (VCCINT), U1.U13 (VCCBRAM), U1.U15 (VCCINT)
VCC1.8: U1.E8 (VCCBATT_0), U1.L11 (VCCAUX), U1.M10 (VCCAUX), U1.M12 (VCCADC_0), U1.P8 (VCCAUX_IO_G0), U1.P10 (VCCAUX), U1.R9 (VCCAUX_IO_G0), U1.T8 (VCCAUX_IO_G0), U1.T10 (VCCAUX), U1.U11 (VCCAUX)
